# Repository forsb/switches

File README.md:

# switches
nodejs and tellstick server for controlling switches from browser

Library for nRF24L01 taken from https://github.com/stanleyseow/RF24

##Pinouts
| nRF24L01 | RPi Physical | Arduino      |  
|----------|--------------|--------------|  
| VCC      | 17           |     3V3 (NOT 5V!)     |  
| GND      | 20           |     GND      |  
| CE       | 18           |     9        |  
| CSN      | 24           |     4        |  
| SCK      | 23           |     13       |  
| MOSI     | 19           |     11       |  
| MISO     | 21           |     12       | 

###Raspberry Pi
- Clone the git repo and run *make*
- Run the *index.js* with Node.js (something like *nodejs index.js*)

###Arduino
All libraries for Arduino are provided in the sketch folder. Open the .ino file in the Arduino IDE and hit *upload*

Libraries used are:
- RF24 by TMRh20 (link:)
- DHT
- 
To use the Arduino sketch, the RF24-library has to be installed. To do so, follow these steps:
- Make sure to have the latest Arduino IDE installed
- Go to *Sketch* -> *Include Library* -> *Manage Libraries*
- Search for *RF24*
- Click on ***RF24*** *by* ***TMRh20***
- Choose latest version and click *install*

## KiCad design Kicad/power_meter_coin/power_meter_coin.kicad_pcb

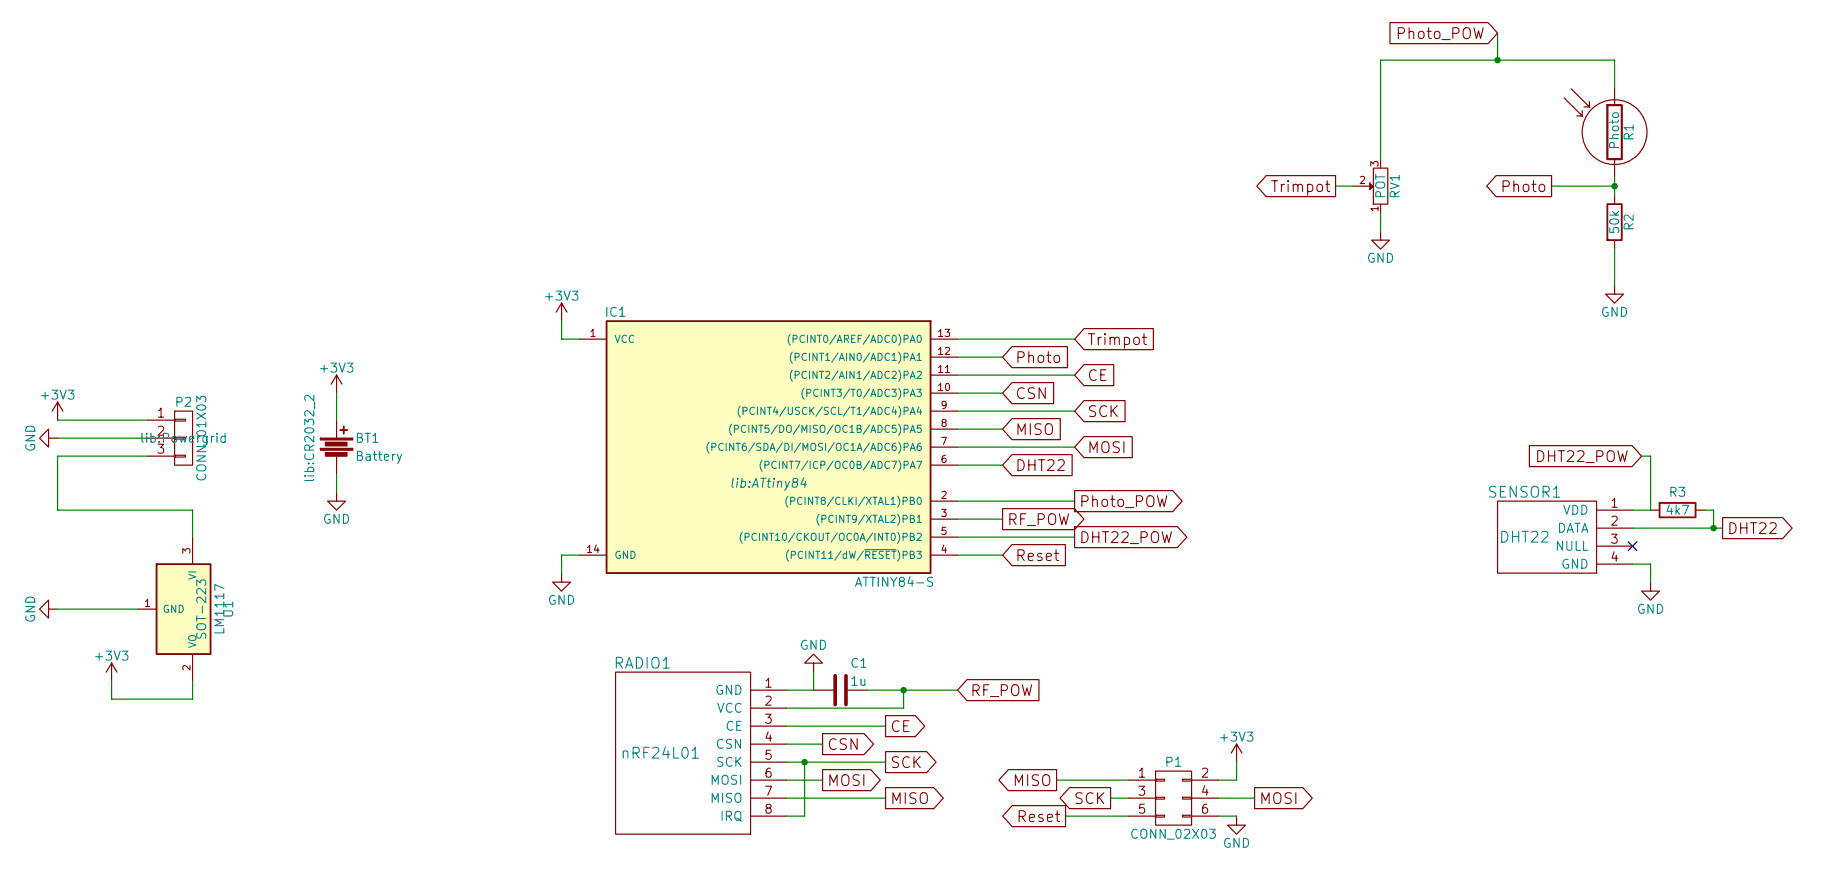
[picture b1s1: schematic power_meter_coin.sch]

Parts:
BT1: Battery; CR2032_2
C1: 1u; C_0805_HandSoldering
IC1: ATTINY84-S; ATtiny84
P1: CONN_02X03; Pin_Header_Straight_2x03
P2: CONN_01X03; Powergrid
R1: Photo; myPhotoRes
R2: 50k; R_0805_HandSoldering
R3: 4k7; R_0805_HandSoldering
RADIO1: nRF24L01
RV1: POT; trimpot
SENSOR1: DHT22
U1: LM1117; SOT-223

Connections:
+3V3: BT1.1, IC1.1 (VCC), P1.2, P2.1, U1.2 (VO)
CE: IC1.11 ((PCINT2/AIN1/ADC2)PA2), RADIO1.3 (CE)
CSN: IC1.10 ((PCINT3/T0/ADC3)PA3), RADIO1.4 (CSN)
DHT22: IC1.6 ((PCINT7/ICP/OC0B/ADC7)PA7), R3.1, SENSOR1.2 (DATA)
DHT22_POW: IC1.5 ((PCINT10/CKOUT/OC0A/INT0)PB2), R3.2, SENSOR1.1 (VDD)
GND: BT1.2, C1.2, IC1.14 (GND), P1.6, P2.2, R2.2, RADIO1.1 (GND), RV1.1, SENSOR1.4 (GND), U1.1 (GND)
MISO: IC1.8 ((PCINT5/DO/MISO/OC1B/ADC5)PA5), P1.1, RADIO1.7 (MISO)
MOSI: IC1.7 ((PCINT6/SDA/DI/MOSI/OC1A/ADC6)PA6), P1.4, RADIO1.6 (MOSI)
unnamed: P2.3, U1.3 (VI)
Photo: IC1.12 ((PCINT1/AIN0/ADC1)PA1), R1.2, R2.1
Photo_POW: IC1.2 ((PCINT8/CLKI/XTAL1)PB0), R1.1, RV1.3
RF_POW: C1.1, IC1.3 ((PCINT9/XTAL2)PB1), RADIO1.2 (VCC)
Reset: IC1.4 ((PCINT11/dW/~RESET~)PB3), P1.5
SCK: IC1.9 ((PCINT4/USCK/SCL/T1/ADC4)PA4), P1.3, RADIO1.5 (SCK), RADIO1.8 (IRQ)
Trimpot: IC1.13 ((PCINT0/AREF/ADC0)PA0), RV1.2

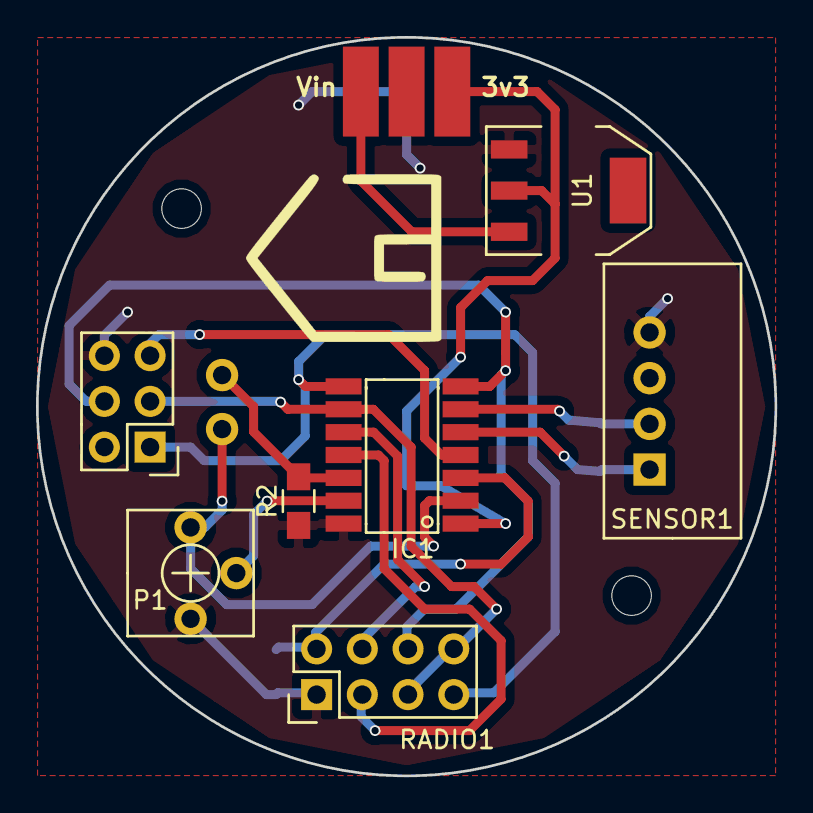
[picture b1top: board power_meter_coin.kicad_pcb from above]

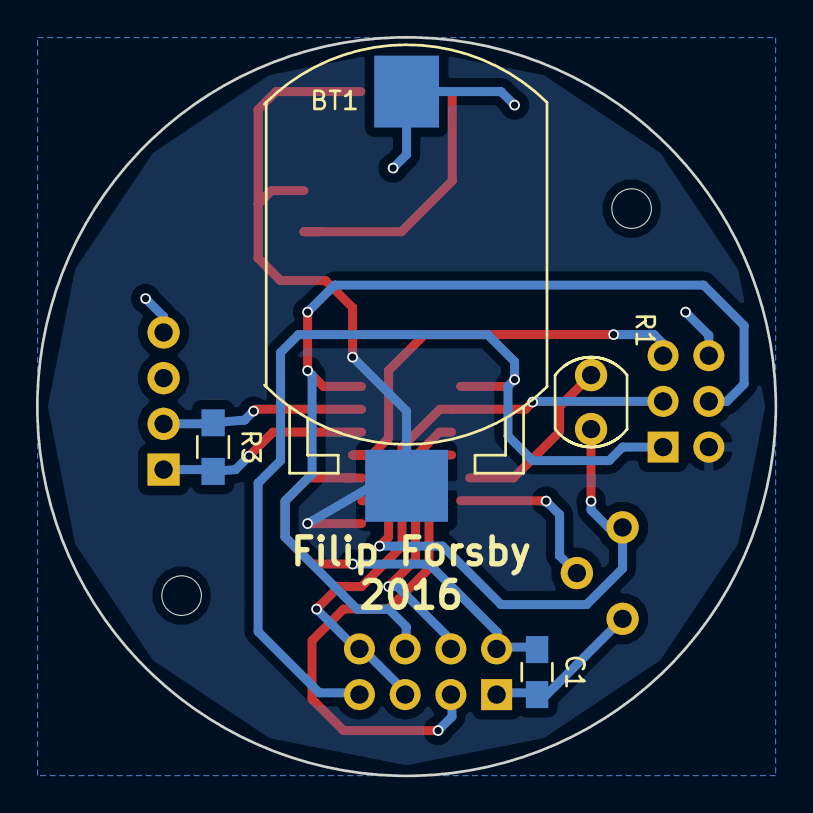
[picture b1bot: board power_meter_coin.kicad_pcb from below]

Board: 2 copper layers, 41.0 x 41.0 mm, 12 parts (4 on the bottom side), 15 nets.

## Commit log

2016-08-29 Moved web to folder and added nodejs script
2016-08-29 removed old web files
2016-08-29 Added install script
2016-08-29 added package.json
2016-08-29 rename and cleanup
2016-08-29 .gitignore
2016-08-29 proper package.json
2016-09-27 will not install git (because already installed when repo is down)
2016-10-05 renamed web to public and index.js now serves public dir
2016-10-07 list all resources working, also removed dbfind function
2016-10-07 web server won't start if db not connected
2016-10-07 remove fail messages if readystate != 4 in web, and added comments to index.js
2016-10-09 ignoring csv file from winscp?
2016-10-12 make web send request to dynamic ip instead of hard coded
2016-10-12 listing a resource with id implemented
2016-10-13 create new resource now working
2016-10-21 added sensorbox
2016-10-21 i dont even know. loadContent
2016-10-22 added chart below sensor boxes
2016-10-24 graph showing time of day data
2016-10-25 removed old graph data
2016-10-25 spawn child with dummy child code in rf directory
2016-10-27 added RF24 library
2016-10-27 Added example code to main.c, made it cpp and did a compile script
2016-10-27 added missing }
2016-10-27 added infinite listening loop (didn't work very well)
2016-10-28 added code from buttonbox to main.cpp
2016-10-29 correct pin numbering for RF24 object
2016-10-29 Added arduino transmitter file
2016-11-03 moved arduino code to folder and tried to send new structure from h-file
2016-11-13 Example of sensor data in db
2016-11-13 added build-essential to install.sh
2016-11-29 added arduino libraries instead of having them installed on computer
2016-12-02 moved database to new fodler
2016-12-02 some errors fixed
2016-12-05 kicad included in git
2016-12-13 ordered version PCB
2016-12-13 cleaned kicad dir
2016-12-16 working DHT22, photo. Also new kicad pcb, as ordered
2016-12-17 working output from arduino
2016-12-17 working input to raspberry
2016-12-22 some more json
2016-12-23 added json output (and indentation)
2016-12-23 fixed dbclinet
2016-12-23 this is not working, but anyway, working with db
